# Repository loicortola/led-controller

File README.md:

# Led Controller

All-in-one OpenSource & Open Hardware Smartphone-controlled Led Controller for ESP-8266.  

## Requirements

The current version has been rewritten entirely in C/C++ to use along with Arduino IDE.

 * Install Arduino IDE
 * [Install ESP8266 model](https://github.com/esp8266/Arduino)
 * [Install ESP8266 Arduino filesystem uploader plugin](https://github.com/esp8266/arduino-esp8266fs-plugin)
 * Install EAGLE or KiCAD (only if you want to edit the board hardware design)
**NB: You can find a previous version for NodeMCU (in LUA) in previous commits.**

## Schematics
This board is Open-Hardware.  
All parts and schematics are available in the hardware folder.  

## Setup

 * Transfer the content using Arduino onto your ESP-8266.
 * Transfer the files in data/ with the filesystem uploader plugin.

Warning: Your ESP needs to be in bootloader mode!

## Setup Instructions

### 1. First setup
At first power-on, your LEDs will be blinking green. Your device is waiting for you to configure it.

Find the Wifi Access-Point named "Led-SOMETHING", and connect to it from your laptop, your smartphone, or any Wireless device.  
Open your browser and access http://10.0.0.1  

Enter your Wifi credentials, and choose a personal password key for your LED controller. This password will be asked everytime you want to bind your controller to an external control system.

When registered, your LED Controller will restart and blink yellow. Yellow means "I am trying to connect with the credentials you gave me".

If the LED Controller succeeds, the light will turn Blue and stop blinking. That means your LED Controller setup is successful.

Otherwise, after 10 seconds, the LEDs will blink red. This means that your settings did not work correctly.
You can safely reboot (take off the plug, and plug it on again) your LED Controller and start over.

### 2. Updates
Any Wifi network/password change will require the LED Controller to be setup once again. This is a safety measure.

### 3. Android App
When you have installed the APK on your phone, simply launch it and click on "Re-Sync" in the settings tab.
Make sure you are connected on the same wifi network as your LED Controller.

When your Controller is successfully found, a Dialog will pop-up so you can enter your password key.

You're done! The Controller is now successfully paired to your Android App!

** Seeking contributions to improve UX and features of the app.**

### Contributors
All contributions are welcome.
If you want to join the project, please let me know on Twitter [@LoicOrtola](https://twitter.com/loicortola) or start sending PRs ;)

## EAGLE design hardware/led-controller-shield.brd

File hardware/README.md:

# Led-Controller Parts

Here are the necessary parts to buy for your Led Controller board:

 * 1x [PJ-002A JACK 2X5.5MM](https://www.digikey.fr/product-detail/en/cui-inc/PJ-002A/CP-002A-ND/96962)
 * 1x [LD1117S33TR - IC REG LINEAR 3.3V 800MA SOT223](https://www.digikey.com/product-detail/en/stmicroelectronics/LD1117S33TR/497-1242-1-ND/586242)
 * 3x [FQD13N06LTM - MOSFET N-CH 60V 11A DPAK](https://www.digikey.com/product-detail/en/on-semiconductor/FQD13N06LTM/FQD13N06LTMCT-ND/3042598)
 * 2x [679-2428-ND - SWITCH TACTILE 12V 0.05A](https://www.digikey.com/product-detail/en/apem-inc/MJTP1230/679-2428-ND/1798037)
 * 4x [RC1206FR-0710KL - 10KOhms 1% RESISTOR 1206](https://www.digikey.fr/product-detail/en/yageo/RC1206FR-0710KL/311-10.0KFRCT-ND/731430)
 * 1x [ESP-8266 - ESP12](https://fr.aliexpress.com/wholesale?catId=0&initiative_id=SB_20171122124705&SearchText=esp12)
 * 1x [15PIN-HEAD](https://fr.aliexpress.com/wholesale?catId=0&initiative_id=SB_20171122124828&SearchText=male+pin+header)

You can also order the PCBs directly from Aisler.net:  
[Board PCB](https://aisler.net/loicortola/led-controller/board-pcb)
[Shield PCB](https://aisler.net/loicortola/led-controller/shield)

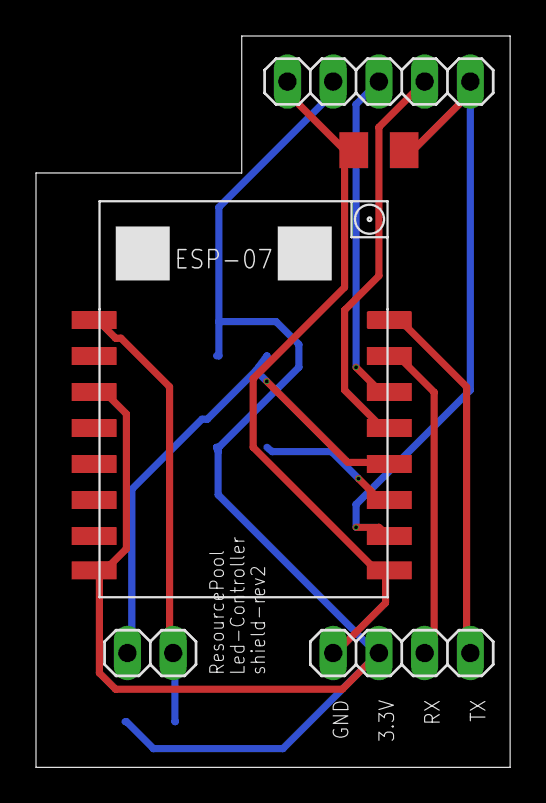
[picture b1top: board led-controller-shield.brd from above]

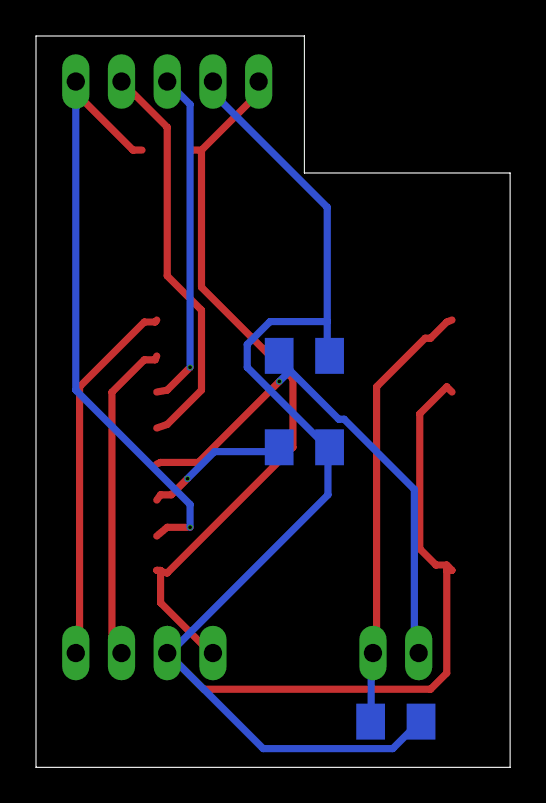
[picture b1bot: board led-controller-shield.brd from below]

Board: 2 copper layers, 26.3 x 40.6 mm, 8 parts (3 on the bottom side), 10 nets.

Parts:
LED-CONTROLLER-SHIELD1:ESP8266: ESP07-16PIN
LED-CONTROLLER-SHIELD1:FLASH: 1X04
LED-CONTROLLER-SHIELD1:JP1: 1X05
LED-CONTROLLER-SHIELD1:JP3: 1X02
LED-CONTROLLER-SHIELD1:R1, LED-CONTROLLER-SHIELD1:R2, LED-CONTROLLER-SHIELD1:R3, LED-CONTROLLER-SHIELD1:R4: 10k; M1206

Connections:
LED-CONTROLLER-SHIELD1:+3.3V: LED-CONTROLLER-SHIELD1:ESP8266.CH_PD, LED-CONTROLLER-SHIELD1:ESP8266.VCC, LED-CONTROLLER-SHIELD1:FLASH.2, LED-CONTROLLER-SHIELD1:JP1.2, LED-CONTROLLER-SHIELD1:R1.2, LED-CONTROLLER-SHIELD1:R3.2, LED-CONTROLLER-SHIELD1:R4.2
LED-CONTROLLER-SHIELD1:B: LED-CONTROLLER-SHIELD1:ESP8266.GPIO15, LED-CONTROLLER-SHIELD1:JP1.5, LED-CONTROLLER-SHIELD1:R2.2
LED-CONTROLLER-SHIELD1:BOOT: LED-CONTROLLER-SHIELD1:ESP8266.GPIO0, LED-CONTROLLER-SHIELD1:JP3.1, LED-CONTROLLER-SHIELD1:R4.1
LED-CONTROLLER-SHIELD1:G: LED-CONTROLLER-SHIELD1:ESP8266.GPIO5, LED-CONTROLLER-SHIELD1:JP1.4
LED-CONTROLLER-SHIELD1:GND: LED-CONTROLLER-SHIELD1:ESP8266.GND, LED-CONTROLLER-SHIELD1:FLASH.1, LED-CONTROLLER-SHIELD1:JP1.1, LED-CONTROLLER-SHIELD1:R2.1
LED-CONTROLLER-SHIELD1:N$6: LED-CONTROLLER-SHIELD1:ESP8266.GPIO2, LED-CONTROLLER-SHIELD1:R3.1
LED-CONTROLLER-SHIELD1:N$8: LED-CONTROLLER-SHIELD1:ESP8266.TX, LED-CONTROLLER-SHIELD1:FLASH.4
LED-CONTROLLER-SHIELD1:N$9: LED-CONTROLLER-SHIELD1:ESP8266.RX, LED-CONTROLLER-SHIELD1:FLASH.3
LED-CONTROLLER-SHIELD1:R: LED-CONTROLLER-SHIELD1:ESP8266.GPIO4, LED-CONTROLLER-SHIELD1:JP1.3
LED-CONTROLLER-SHIELD1:RST: LED-CONTROLLER-SHIELD1:ESP8266.REST, LED-CONTROLLER-SHIELD1:JP3.2, LED-CONTROLLER-SHIELD1:R1.1

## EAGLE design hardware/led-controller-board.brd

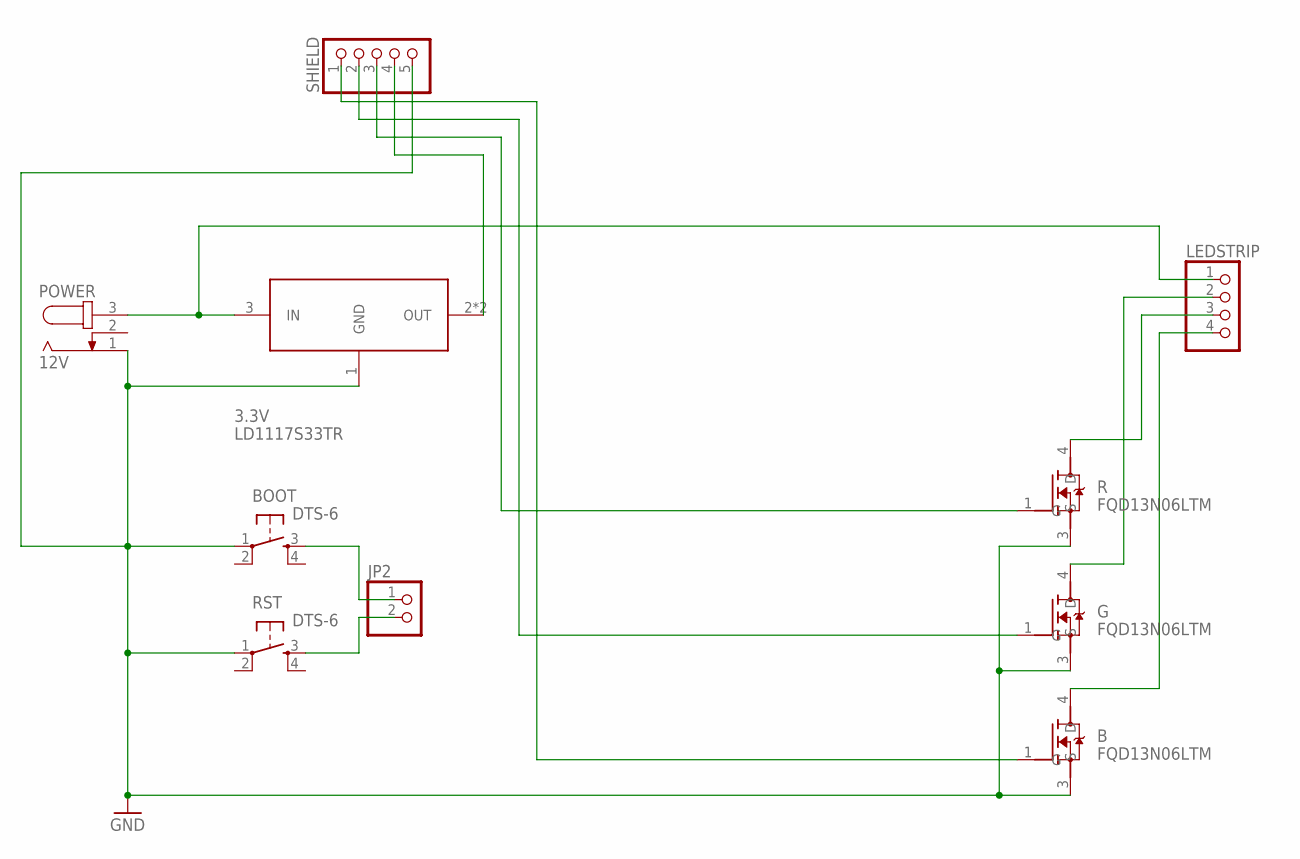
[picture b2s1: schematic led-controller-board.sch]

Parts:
3.3V: LD1117S33TR; SOT223
B: FQD13N06LTM; TO229P991X239-3N
BOOT: DTS-6
G: FQD13N06LTM; TO229P991X239-3N
JP2: PINHD-1X2; 1X02
LEDSTRIP: PINHD-1X4/90; 1X04/90
POWER: 12V; SPC4078
R: FQD13N06LTM; TO229P991X239-3N
RST: DTS-6
SHIELD: PINHD-1X5; 1X05

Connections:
GND: 3.3V.1 (GND), B.3 (S), BOOT.1, G.3 (S), POWER.1, R.3 (S), RST.1, SHIELD.5
unnamed: 3.3V.3 (IN), LEDSTRIP.1, POWER.3
unnamed: BOOT.3, JP2.1
unnamed: JP2.2, RST.3
unnamed: 3.3V.2 (OUT), 3.3V.4 (OUT), SHIELD.4
unnamed: B.1 (G), SHIELD.1
unnamed: R.1 (G), SHIELD.3
unnamed: G.1 (G), SHIELD.2
unnamed: G.4 (D), LEDSTRIP.2
unnamed: LEDSTRIP.3, R.4 (D)
unnamed: B.4 (D), LEDSTRIP.4

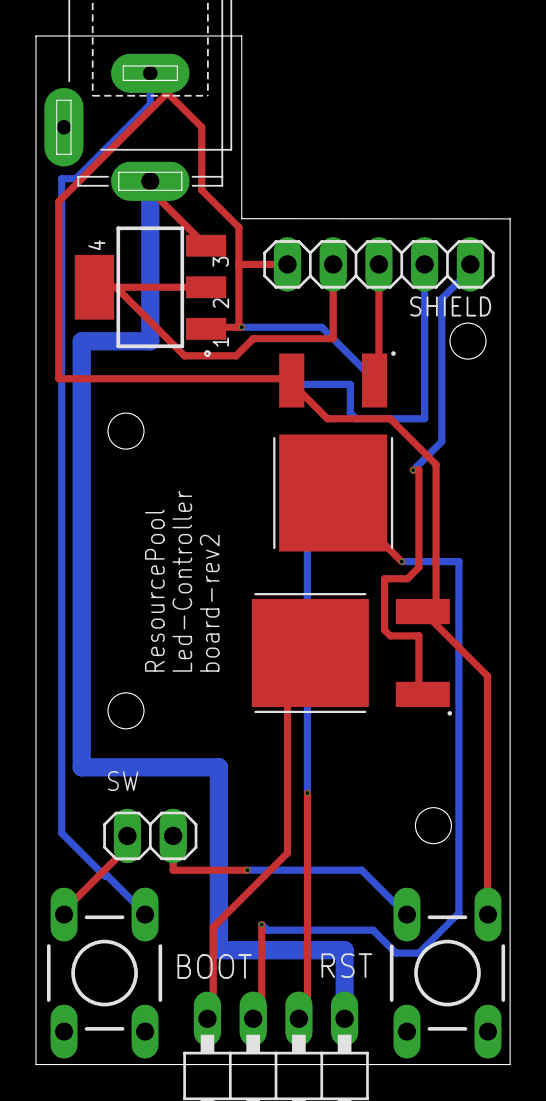
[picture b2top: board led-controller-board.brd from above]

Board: 2 copper layers, 26.3 x 57.1 mm, 10 parts (1 on the bottom side), 11 nets.

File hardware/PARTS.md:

# Led-Controller Parts

Here are the necessary parts to buy for your Led Controller board:

 * 1x [PJ-002A JACK 2X5.5MM](https://www.digikey.fr/product-detail/en/cui-inc/PJ-002A/CP-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
 * 1x [LD1117S33TR - IC REG LINEAR 3.3V 800MA SOT223](https://www.digikey.com/product-detail/en/stmicroelectronics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
 * 3x [FQD13N06LTM - MOSFET N-CH 60V 11A DPAK](https://www.digikey.com/product-detail/en/on-semiconductor/F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
 * 2x [679-2428-ND - SWITCH TACTILE 12V 0.05A](https://www.digikey.com/product-detail/en/apem-inc/MJTP1230/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
 * 4x [RC1206FR-0710KL - 10KOhms 1% RESISTOR 1206](https://www.digikey.fr/product-detail/en/yageo/RC1206FR-0710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
 * 1x [ESP-8266 - ESP12](https://fr.aliexpress.com/wholesale?catId=0&initiative_id=SB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
 * 1x [15PIN-HEAD](https://fr.aliexpress.com/wholesale?catId=0&initiative_id=SB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

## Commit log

2015-12-21 Added base project. WIP
2015-12-25 Working http-server
2016-01-15 Working http server with no leak
2016-01-24 Deleted espress content, Refactored API
2016-02-16 Added android base app
2016-03-27 Added Wifi setup process
2016-03-27 Added mDNS registration, Updated README.md
2016-03-27 Added ON/OFF Switch
2016-03-27 Added Switch and multicast DNS Lookup features in Android app
2016-03-28 Refactored Android app... Aoutch
2017-07-30 WIP Switched from NodeMCU to ESP + Arduino
    Complete rewrite in C/C++
2017-07-31 Added ApiKey support, fixed Password issue, WIP for AnimationSet
2017-08-01 Fixed leaks, implemented AnimationSet
2017-08-01 Removed utils, cleaned code
2017-08-02 Fixed really cool bugs. Divide by zero, animation flaws
2017-08-02 Oops
2017-08-05 Fixed android issues on legacy app
2017-08-06 Refactored android app: now supports SSDP Discovery
2017-08-06 Added presets to android App
2017-08-06 Fixed API
2017-08-08 Added Mock flavor
2017-10-15 Added screenshots and contributors wanted mention
    Resized images
2017-11-12 Fixed NPE and changed theme to Dark
2017-11-22 Added schematics rev2, changed README
2017-11-22 Updated screenshots, added custom name
2017-12-04 [Release:1.0.0] Version upgrades
